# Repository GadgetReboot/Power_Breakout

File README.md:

# Power_Breakout
<br><br><BR><BR>
Power jack/screw terminal distribution PCB with PTC resettable fuses

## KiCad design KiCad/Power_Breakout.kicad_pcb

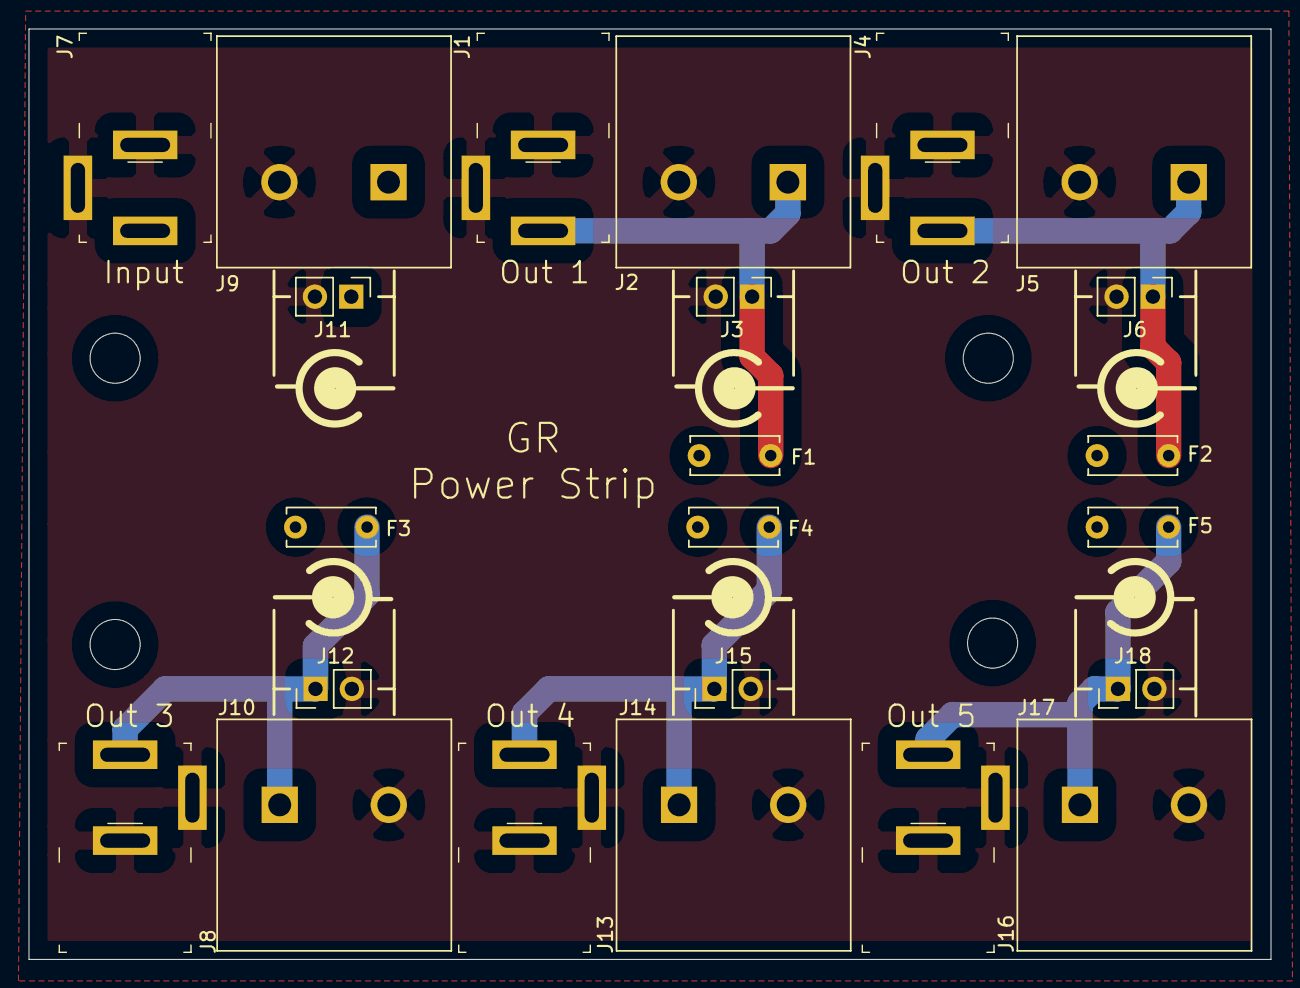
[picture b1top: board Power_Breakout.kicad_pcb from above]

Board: 2 copper layers, 86.8 x 65.0 mm, 27 parts (0 on the bottom side), 7 nets.

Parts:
F1, F2, F3, F4, F5: Polyfuse; C_Disc_D6.0mm_W2.5mm_P5.00mm
H1, H2, H3, H4: MountingHole; MountingHole_3.5mm
J1, J4, J7, J8, J13, J16: PJ-202A; Barrel_Jack_5.5mmODx2.1mmID_PJ-202A
J2, J5, J9, J10, J14, J17: T70243500000G; TerminalBlock_2P_P7.62mm
J3, J6, J11, J12, J15, J18: Conn_01x02; PinHeader_1x02_P2.54mm_Vertical

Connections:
unnamed: F1.1, J1.1, J2.1, J3.1
unnamed: F1.2, F2.2, F3.2, F4.2, F5.2, J7.1, J9.1, J11.1
unnamed: F2.1, J4.1, J5.1, J6.1
unnamed: F3.1, J8.1, J10.1, J12.1
unnamed: F4.1, J13.1, J14.1, J15.1
unnamed: F5.1, J16.1, J17.1, J18.1
unnamed: J1.2, J1.3, J2.2, J3.2, J4.2, J4.3, J5.2, J6.2, J7.2, J7.3, J8.2, J8.3, J9.2, J10.2, J11.2, J12.2, J13.2, J13.3, J14.2, J15.2, J16.2, J16.3, J17.2, J18.2
